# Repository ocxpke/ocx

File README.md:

# OCX handheld: main board

Main PCB of OCX, a PSP-style handheld console designed for my bachelor's thesis (TFG).

## What's on the board
- **MCU:** ESP32-S3-DevKitC-1 on two 1×22 sockets. Its antenna sits over a cutout in the board edge.
- **Display:** BT817Q (EVE4) graphics controller with a W25Q128JV flash and a 12 MHz crystal. It drives a 5" 800×480 RGB panel (NHD-5.0-800480AF-ASXP-CTP) through a 40-pin FPC, and its capacitive touch through a 6-pin FPC.
- **Backlight:** DIO5661 constant-current boost, ~60 mA at ~21 V.
- **Power:** USB-C, 5 V only, with USBLC6-2 ESD protection. An LMR51430 buck makes the 3.3 V rail.
- **Input:** MCP23017 I²C expander for 14 buttons, plus two analog joysticks on FPCs.
- **Audio:** PAM8302A class-D amplifier with a JST PH speaker connector.

## Board
| | |
|---|---|
| EDA | KiCad 10.0 (the files don't open in KiCad 9 or older) |
| Layers | 4: F.Cu signals / In1 GND / In2 3.3 V / B.Cu signals |
| Size | 228 × 115.4 mm, 1.6 mm thick |
| Fab | JLCPCB, JLC04161H-2116 stackup, ENIG |

## Opening the project
Install KiCad 10.0 and open `hardware/ocxPrototype.kicad_pro`.
All footprints and 3D models come from the standard KiCad libraries. The only custom symbol (BT817Q) is in `hardware/EVE_custom.kicad_sym`, registered in the project's `sym-lib-table`.

## License

Copyright © 2026 Jose Ramirez Giron

**Hardware** (everything in `hardware/`: schematics, PCB layout and symbol library) is licensed under the
[CERN Open Hardware Licence Version 2 – Strongly Reciprocal (CERN-OHL-S-2.0)](https://ohwr.org/cern_ohl_s_v2.txt).
See [`LICENSE`](LICENSE) for the full text.

You may use, study, modify, manufacture and sell this design or products based on it, as long as you:
- keep the copyright and licence notices,
- make the source of any modified version available under the same licence, and
- state clearly what you changed and when.

**Documentation and images** (`docs/`) are licensed under
[Creative Commons Attribution-ShareAlike 4.0 (CC BY-SA 4.0)](https://creativecommons.org/licenses/by-sa/4.0/).

"OCX" is the name of this project. Please don't use it for modified versions or present them as the original.

Datasheets of third-party components belong to their manufacturers and are not covered by these licences.

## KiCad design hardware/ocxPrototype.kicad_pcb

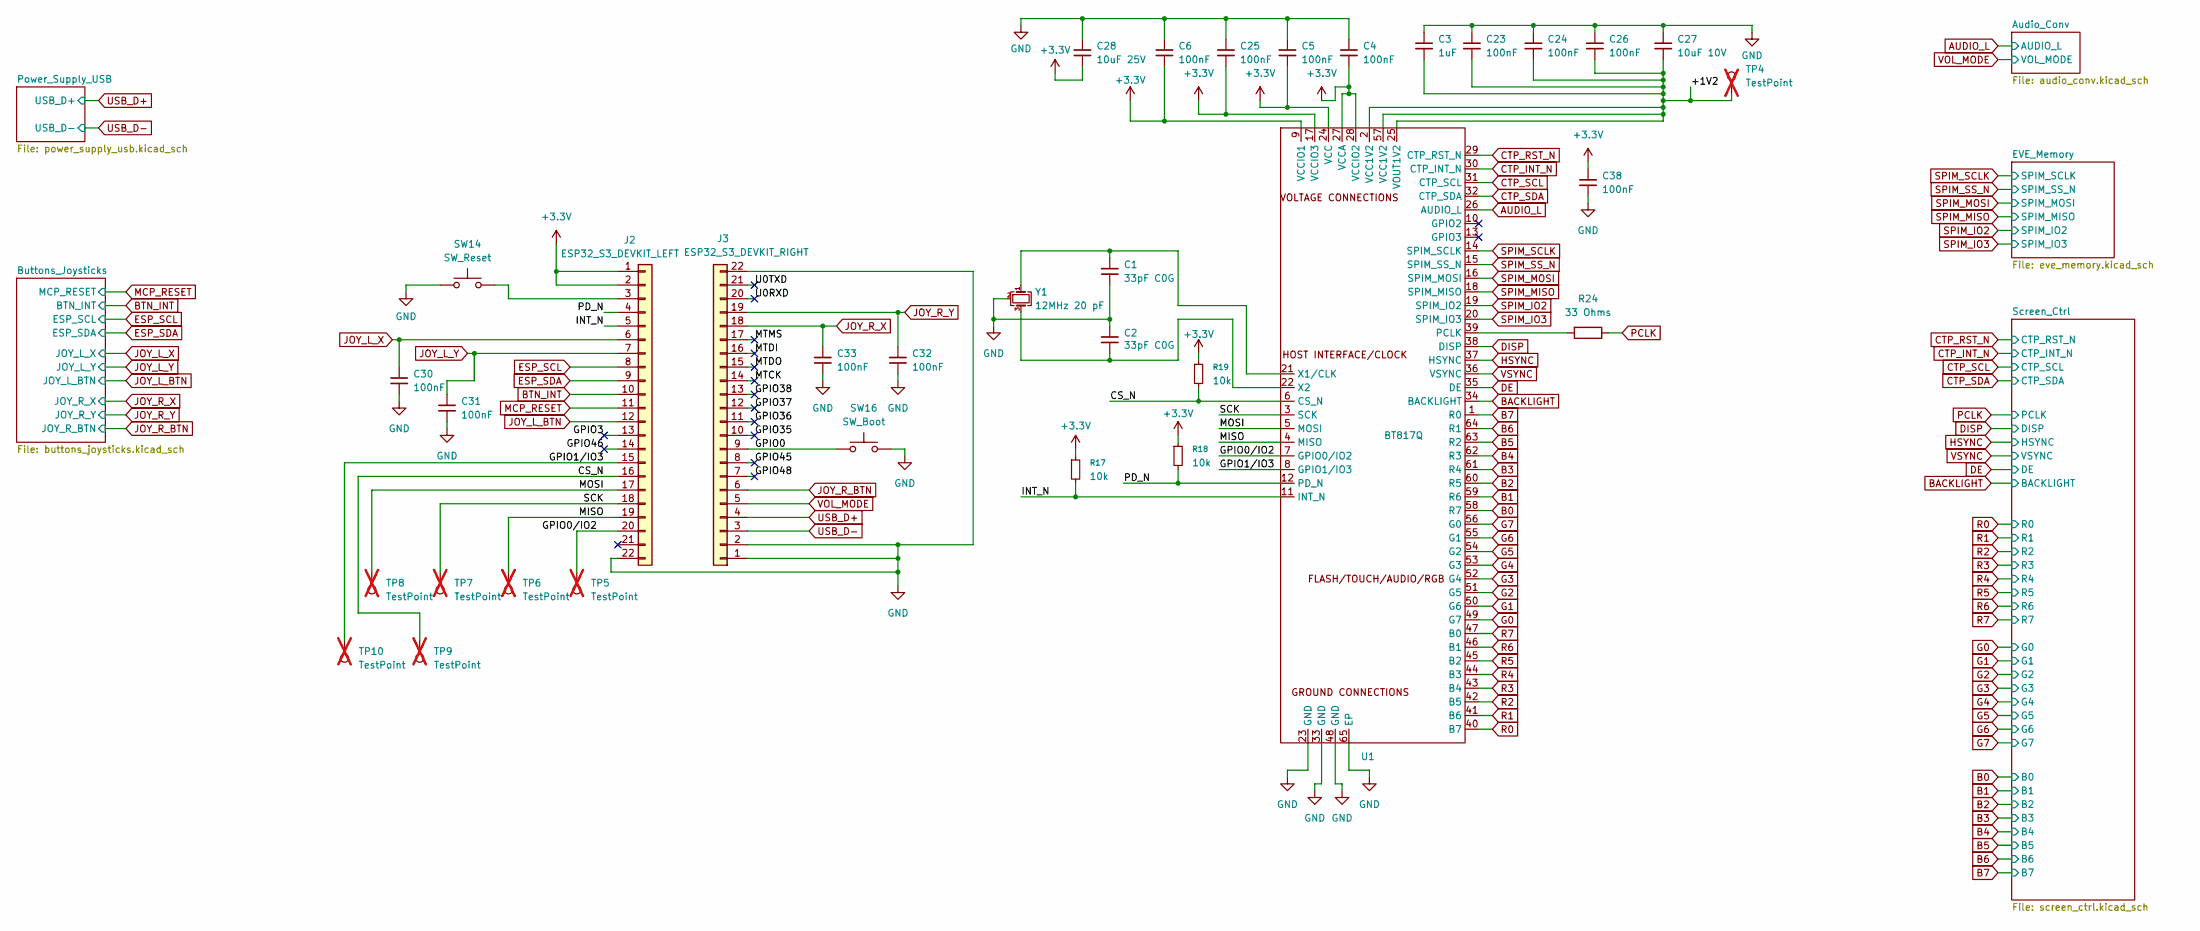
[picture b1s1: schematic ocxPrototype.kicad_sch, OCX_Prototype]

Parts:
C1, C2: 33pF C0G; C_0402_1005Metric; MPN 0402CG330J500NT; LCSC C1562
C3: 1uF; C_0402_1005Metric; MPN CL05A105KA5NQNC; LCSC C52923
C4, C5, C6, C23, C24, C25, C26: 100nF; C_0402_1005Metric; MPN CL05B104KO5NNNC; LCSC C1525
C27: 10uF 10V; C_0603_1608Metric; MPN CL10A106KP8NNNC; LCSC C19702
C28: 10uF 25V; C_0805_2012Metric_Pad1.18x1.45mm_HandSolder; MPN CL21A106KAYNNNE; LCSC C15850
C30, C31, C32, C33, C38: 100nF; C_0805_2012Metric_Pad1.18x1.45mm_HandSolder; MPN CC0805KRX7R9BB104; LCSC C49678
J2: ESP32_S3_DEVKIT_LEFT; PinSocket_1x22_P2.54mm_Vertical; MPN FH2.54-09-22PZD; LCSC C7500786
J3: ESP32_S3_DEVKIT_RIGHT; PinSocket_1x22_P2.54mm_Vertical; MPN FH2.54-09-22PZD; LCSC C7500786
R17, R18, R19: 10k; R_0805_2012Metric_Pad1.20x1.40mm_HandSolder; MPN 0805W8F1002T5E; LCSC C17414
R24: 33 Ohms; R_0402_1005Metric; MPN 0402WGF330JTCE; LCSC C25105
SW14: SW_Reset; SW_PUSH_6mm; MPN MLD-TS-6X6X5-J; LCSC C52750873
SW16: SW_Boot; SW_PUSH_6mm; MPN MLD-TS-6X6X5-J; LCSC C52750873
TP4: TestPoint; TestPoint_Pad_D1.5mm; not fitted
TP5, TP6, TP7, TP8, TP9, TP10: TestPoint; TestPoint_Pad_D1.0mm; not fitted
U1: BT817Q; VQFN-64-1EP_9x9mm_P0.5mm_EP5.4x5.4mm_ThermalVias; MPN BT817Q-R; LCSC C20613585
Y1: 12MHz 20 pF; Crystal_SMD_5032-4Pin_5.0x3.2mm; MPN X503212MSB4SI; LCSC C112588

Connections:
+3.3V: C4.2, C5.2, C6.2, C25.2, C28.2, C38.1, J2.1, J2.2, R17.1, R18.1, R19.1, U1.9 (VCCIO1), U1.17 (VCCIO3), U1.24 (VCC), U1.27 (VCCA), U1.28 (VCCIO2); also elsewhere on the board
/+1V2: C3.2, C23.2, C24.2, C26.2, C27.2, TP4.1 (1_1), U1.2 (VCC1V2), U1.25 (VOUT1V2), U1.57 (VCC1V2)
/CS_N: J2.16, R19.2, TP9.1 (1_1), U1.6 (CS_N)
/GPIO0: J3.9, SW16.1
/GPIO0/IO2: J2.20, TP5.1 (1_1), U1.7 (GPIO0/IO2)
/GPIO1/IO3: J2.15, TP10.1 (1_1), U1.8 (GPIO1/IO3)
/GPIO3: J2.13
/GPIO35: J3.10
/GPIO36: J3.11
/GPIO37: J3.12
/GPIO38: J3.13
/GPIO45: J3.8
/GPIO46: J2.14
/GPIO48: J3.7
/INT_N: J2.5, R17.2, U1.11 (INT_N)
/MISO: J2.19, TP6.1 (1_1), U1.4 (MISO)
/MOSI: J2.17, TP8.1 (1_1), U1.5 (MOSI)
/MTCK: J3.14
/MTDI: J3.16
/MTDO: J3.15
/MTMS: J3.17
/PD_N: J2.4, R18.2, U1.12 (PD_N)
/SCK: J2.18, TP7.1 (1_1), U1.3 (SCK)
/U0RXD: J3.20
/U0TXD: J3.21
AUDIO_L: U1.26 (AUDIO_L); also elsewhere on the board
B0: U1.58 (R7); also elsewhere on the board
B1: U1.59 (R6); also elsewhere on the board
B2: U1.60 (R5); also elsewhere on the board
B3: U1.61 (R4); also elsewhere on the board
B4: U1.62 (R3); also elsewhere on the board
B5: U1.63 (R2); also elsewhere on the board
B6: U1.64 (R1); also elsewhere on the board
B7: U1.1 (R0); also elsewhere on the board
BACKLIGHT: U1.34 (BACKLIGHT); also elsewhere on the board
BTN_INT: J2.10; also elsewhere on the board
CTP_INT_N: U1.30 (CTP_INT_N); also elsewhere on the board
CTP_RST_N: U1.29 (CTP_RST_N); also elsewhere on the board
CTP_SCL: U1.31 (CTP_SCL); also elsewhere on the board
CTP_SDA: U1.32 (CTP_SDA); also elsewhere on the board
DE: U1.35 (DE); also elsewhere on the board
DISP: U1.38 (DISP); also elsewhere on the board
ESP_SCL: J2.8; also elsewhere on the board
ESP_SDA: J2.9; also elsewhere on the board
G0: U1.49 (G7); also elsewhere on the board
G1: U1.50 (G6); also elsewhere on the board
G2: U1.51 (G5); also elsewhere on the board
G3: U1.52 (G4); also elsewhere on the board
G4: U1.53 (G3); also elsewhere on the board
G5: U1.54 (G2); also elsewhere on the board
G6: U1.55 (G1); also elsewhere on the board
G7: U1.56 (G0); also elsewhere on the board
GND: C1.1, C2.2, C3.1, C4.1, C5.1, C6.1, C23.1, C24.1, C25.1, C26.1, C27.1, C28.1, C30.2, C31.2, C32.2, C33.2, C38.2, J2.22, J3.1, J3.2, J3.22, SW14.1, SW16.2, U1.23 (GND), U1.33 (GND), U1.48 (GND), U1.65 (EP), Y1.2 (G), Y1.4 (G); also elsewhere on the board
HSYNC: U1.37 (HSYNC); also elsewhere on the board
JOY_L_BTN: J2.12; also elsewhere on the board
JOY_L_X: C30.1, J2.6; also elsewhere on the board
JOY_L_Y: C31.1, J2.7; also elsewhere on the board
JOY_R_BTN: J3.6; also elsewhere on the board
JOY_R_X: C33.1, J3.18; also elsewhere on the board
JOY_R_Y: C32.1, J3.19; also elsewhere on the board
MCP_RESET: J2.11; also elsewhere on the board
unnamed: J2.3, SW14.2
unnamed: R24.2, U1.39 (PCLK)
unnamed: C1.2, U1.21 (X1/CLK), Y1.1
unnamed: C2.1, U1.22 (X2), Y1.3
PCLK: R24.1; also elsewhere on the board
R0: U1.40 (B7); also elsewhere on the board
R1: U1.41 (B6); also elsewhere on the board
R2: U1.42 (B5); also elsewhere on the board
R3: U1.43 (B4); also elsewhere on the board
R4: U1.44 (B3); also elsewhere on the board
R5: U1.45 (B2); also elsewhere on the board
R6: U1.46 (B1); also elsewhere on the board
R7: U1.47 (B0); also elsewhere on the board
SPIM_IO2: U1.19 (SPIM_IO2); also elsewhere on the board
SPIM_IO3: U1.20 (SPIM_IO3); also elsewhere on the board
SPIM_MISO: U1.18 (SPIM_MISO); also elsewhere on the board
SPIM_MOSI: U1.16 (SPIM_MOSI); also elsewhere on the board
SPIM_SCLK: U1.14 (SPIM_SCLK); also elsewhere on the board
SPIM_SS_N: U1.15 (SPIM_SS_N); also elsewhere on the board
USB_D+: J3.4; also elsewhere on the board
USB_D-: J3.3; also elsewhere on the board
VOL_MODE: J3.5; also elsewhere on the board
VSYNC: U1.36 (VSYNC); also elsewhere on the board

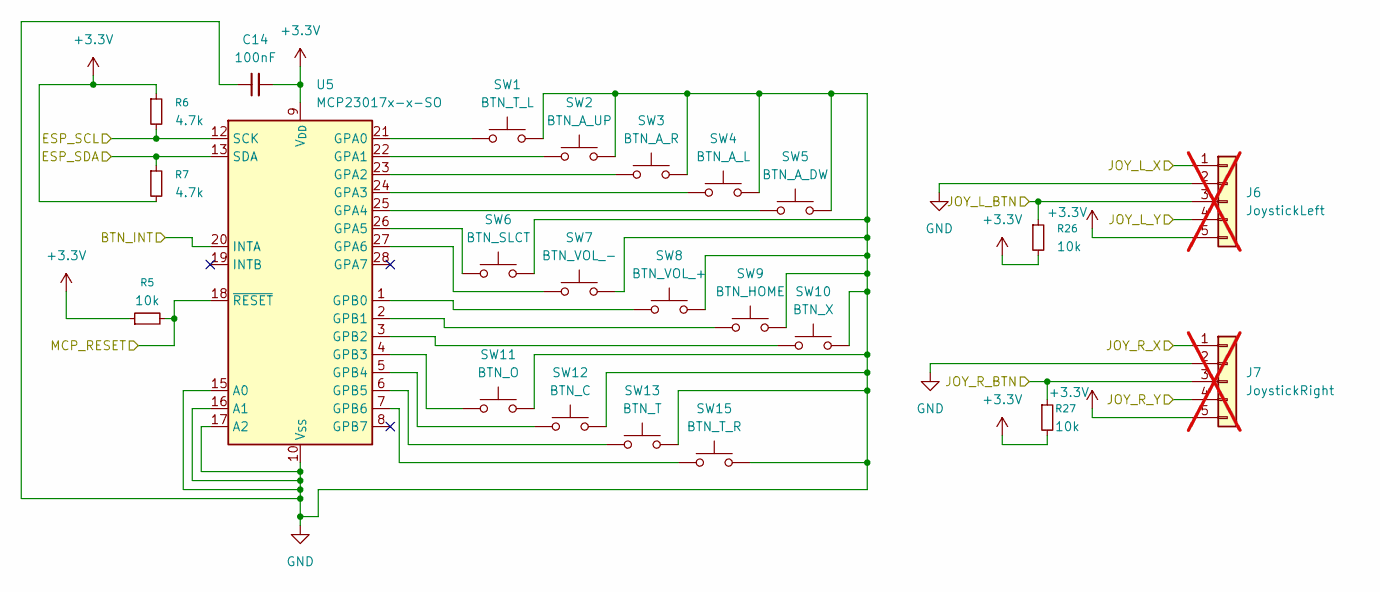
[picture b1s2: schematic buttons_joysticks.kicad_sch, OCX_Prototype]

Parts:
C14: 100nF; C_0805_2012Metric_Pad1.18x1.45mm_HandSolder; MPN CC0805KRX7R9BB104; LCSC C49678
J6: JoystickLeft; TE_0-1734839-5_1x05-1MP_P0.5mm_Horizontal; MPN SFV5R-4STE1HLF; not fitted
J7: JoystickRight; TE_0-1734839-5_1x05-1MP_P0.5mm_Horizontal; MPN SFV5R-4STE1HLF; not fitted
R5, R26, R27: 10k; R_0805_2012Metric_Pad1.20x1.40mm_HandSolder; MPN 0805W8F1002T5E; LCSC C17414
R6, R7: 4.7k; R_0805_2012Metric_Pad1.20x1.40mm_HandSolder; MPN 0805W8F4701T5E; LCSC C17673
SW1: BTN_T_L; SW_PUSH_6mm; MPN MLD-TS-6X6X5-J; LCSC C52750873
SW2: BTN_A_UP; SW_PUSH_6mm; MPN MLD-TS-6X6X5-J; LCSC C52750873
SW3: BTN_A_R; SW_PUSH_6mm; MPN MLD-TS-6X6X5-J; LCSC C52750873
SW4: BTN_A_L; SW_PUSH_6mm; MPN MLD-TS-6X6X5-J; LCSC C52750873
SW5: BTN_A_DW; SW_PUSH_6mm; MPN MLD-TS-6X6X5-J; LCSC C52750873
SW6: BTN_SLCT; SW_PUSH_6mm; MPN MLD-TS-6X6X5-J; LCSC C52750873
SW7: BTN_VOL_-; SW_PUSH_6mm; MPN MLD-TS-6X6X5-J; LCSC C52750873
SW8: BTN_VOL_+; SW_PUSH_6mm; MPN MLD-TS-6X6X5-J; LCSC C52750873
SW9: BTN_HOME; SW_PUSH_6mm; MPN MLD-TS-6X6X5-J; LCSC C52750873
SW10: BTN_X; SW_PUSH_6mm; MPN MLD-TS-6X6X5-J; LCSC C52750873
SW11: BTN_O; SW_PUSH_6mm; MPN MLD-TS-6X6X5-J; LCSC C52750873
SW12: BTN_C; SW_PUSH_6mm; MPN MLD-TS-6X6X5-J; LCSC C52750873
SW13: BTN_T; SW_PUSH_6mm; MPN MLD-TS-6X6X5-J; LCSC C52750873
SW15: BTN_T_R; SW_PUSH_6mm; MPN MLD-TS-6X6X5-J; LCSC C52750873
U5: MCP23017x-x-SO; SOIC-28W_7.5x17.9mm_P1.27mm; MPN MCP23017-E/SO; LCSC C47023

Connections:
+3.3V: C14.2, J6.5, J7.5, R5.1, R6.1, R7.2, R26.2, R27.2, U5.9 (V_{DD}); also elsewhere on the board
BTN_INT: U5.20 (INTA); also elsewhere on the board
ESP_SCL: R6.2, U5.12 (SCK); also elsewhere on the board
ESP_SDA: R7.1, U5.13 (SDA); also elsewhere on the board
GND: C14.1, J6.2, J7.2, SW1.2, SW2.2, SW3.2, SW4.2, SW5.2, SW6.2, SW7.2, SW8.2, SW9.2, SW10.2, SW11.2, SW12.2, SW13.2, SW15.2, U5.10 (V_{SS}), U5.15 (A0), U5.16 (A1), U5.17 (A2); also elsewhere on the board
JOY_L_BTN: J6.3, R26.1; also elsewhere on the board
JOY_L_X: J6.1; also elsewhere on the board
JOY_L_Y: J6.4; also elsewhere on the board
JOY_R_BTN: J7.3, R27.1; also elsewhere on the board
JOY_R_X: J7.1; also elsewhere on the board
JOY_R_Y: J7.4; also elsewhere on the board
MCP_RESET: R5.2, U5.18 (~RESET); also elsewhere on the board
unnamed: SW1.1, U5.21 (GPA0)
unnamed: SW2.1, U5.22 (GPA1)
unnamed: SW3.1, U5.23 (GPA2)
unnamed: SW4.1, U5.24 (GPA3)
unnamed: SW5.1, U5.25 (GPA4)
unnamed: SW6.1, U5.26 (GPA5)
unnamed: SW7.1, U5.27 (GPA6)
unnamed: SW8.1, U5.1 (GPB0)
unnamed: SW9.1, U5.2 (GPB1)
unnamed: SW10.1, U5.3 (GPB2)
unnamed: SW11.1, U5.4 (GPB3)
unnamed: SW12.1, U5.5 (GPB4)
unnamed: SW13.1, U5.6 (GPB5)
unnamed: SW15.1, U5.7 (GPB6)

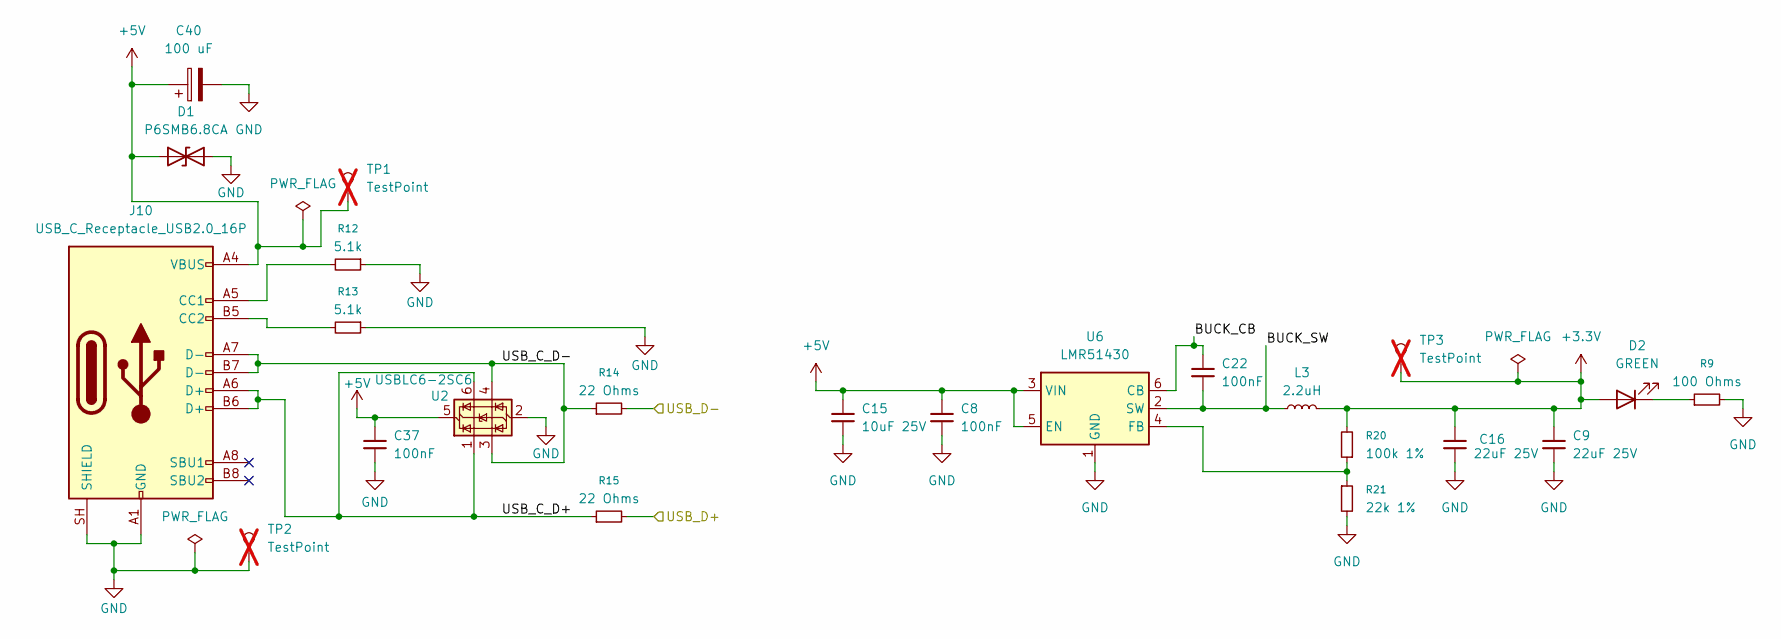
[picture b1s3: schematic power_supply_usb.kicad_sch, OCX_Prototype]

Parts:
C8, C22, C37: 100nF; C_0805_2012Metric_Pad1.18x1.45mm_HandSolder; MPN CC0805KRX7R9BB104; LCSC C49678
C9, C16: 22uF 25V; C_0805_2012Metric_Pad1.18x1.45mm_HandSolder; MPN CL21A226MAQNNNE; LCSC C45783
C15: 10uF 25V; C_0805_2012Metric_Pad1.18x1.45mm_HandSolder; MPN CL21A106KAYNNNE; LCSC C15850
C40: 100 uF; CP_Elec_6.3x5.8; MPN MA16V100M6X6; LCSC C46550460
D1: P6SMB6.8CA; D_SMB_Handsoldering; MPN P6SMB6.8CA/TR13; LCSC C78395
D2: GREEN; LED_0805_2012Metric_Pad1.15x1.40mm_HandSolder; MPN KT-0805G; LCSC C2297
J10: USB_C_Receptacle_USB2.0_16P; USB_C_Receptacle_HRO_TYPE-C-31-M-12; MPN TYPE-C-31-M-12; LCSC C165948
L3: 2.2uH; L_Coilcraft_XxL4020; MPN XAL4020-222MEC; LCSC C3151182
R9: 100 Ohms; R_0805_2012Metric_Pad1.20x1.40mm_HandSolder; MPN 0805W8F1000T5E; LCSC C17408
R12, R13: 5.1k; R_0805_2012Metric_Pad1.20x1.40mm_HandSolder; MPN 0805W8F5101T5E; LCSC C27834
R14, R15: 22 Ohms; R_0805_2012Metric_Pad1.20x1.40mm_HandSolder; MPN 0805W8F220JT5E; LCSC C17561
R20: 100k 1%; R_0805_2012Metric_Pad1.20x1.40mm_HandSolder; MPN 0805W8F1003T5E; LCSC C149504
R21: 22k 1%; R_0805_2012Metric_Pad1.20x1.40mm_HandSolder; MPN 0805W8F2202T5E; LCSC C17560
TP1, TP3: TestPoint; TestPoint_Pad_D1.5mm; not fitted
TP2: TestPoint; TestPoint_Keystone_5000-5004_Miniature; not fitted
U2: USBLC6-2SC6; SOT-23-6; MPN USBLC6-2SC6; LCSC C7519
U6: LMR51430; SOT-23-6; MPN LMR51430YDDCR; LCSC C5210749

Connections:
+3.3V: C9.1, C16.1, D2.2 (A), L3.2, R20.2, TP3.1 (1_1); also elsewhere on the board
/Power_Supply_USB/BUCK_CB: C22.1, U6.6 (CB)
/Power_Supply_USB/BUCK_SW: C22.2, L3.1, U6.2 (SW)
/Power_Supply_USB/USB_C_D+: J10.A6 (D+), J10.B6 (D+), R15.1, U2.1 (I/O1), U2.6 (I/O1)
/Power_Supply_USB/USB_C_D-: J10.A7 (D-), J10.B7 (D-), R14.1, U2.3 (I/O2), U2.4 (I/O2)
GND: C8.2, C9.2, C15.2, C16.2, C37.2, C40.2, D1.2 (A2), J10.A1 (GND), J10.A12 (GND), J10.B1 (GND), J10.B12 (GND), J10.SH (SHIELD), R9.2, R12.1, R13.1, R21.2, TP2.1 (1_1), U2.2 (GND), U6.1 (GND); also elsewhere on the board
unnamed: D2.1 (K), R9.1
unnamed: J10.A5 (CC1), R12.2
unnamed: J10.B5 (CC2), R13.2
unnamed: R20.1, R21.1, U6.4 (FB)
USB_D+: R15.2; also elsewhere on the board
USB_D-: R14.2; also elsewhere on the board

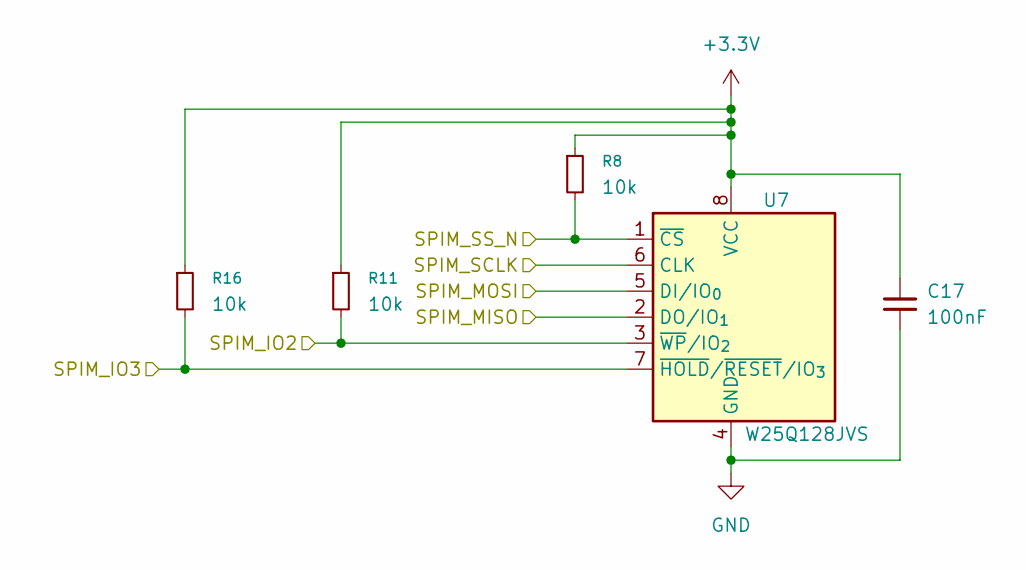
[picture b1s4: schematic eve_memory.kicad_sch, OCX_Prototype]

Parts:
C17: 100nF; C_0402_1005Metric; MPN CL05B104KO5NNNC; LCSC C1525
R8, R11, R16: 10k; R_0805_2012Metric_Pad1.20x1.40mm_HandSolder; MPN 0805W8F1002T5E; LCSC C17414
U7: W25Q128JVS; SOIC-8_5.3x5.3mm_P1.27mm; MPN W25Q128JVSIQ; LCSC C97521

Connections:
+3.3V: C17.1, R8.1, R11.1, R16.1, U7.8 (VCC); also elsewhere on the board
GND: C17.2, U7.4 (GND); also elsewhere on the board
SPIM_IO2: R11.2, U7.3 (~WP/IO_{2}); also elsewhere on the board
SPIM_IO3: R16.2, U7.7 (~HOLD/~RESET/IO_{3}); also elsewhere on the board
SPIM_MISO: U7.2 (DO/IO_{1}); also elsewhere on the board
SPIM_MOSI: U7.5 (DI/IO_{0}); also elsewhere on the board
SPIM_SCLK: U7.6 (CLK); also elsewhere on the board
SPIM_SS_N: R8.2, U7.1 (~CS); also elsewhere on the board

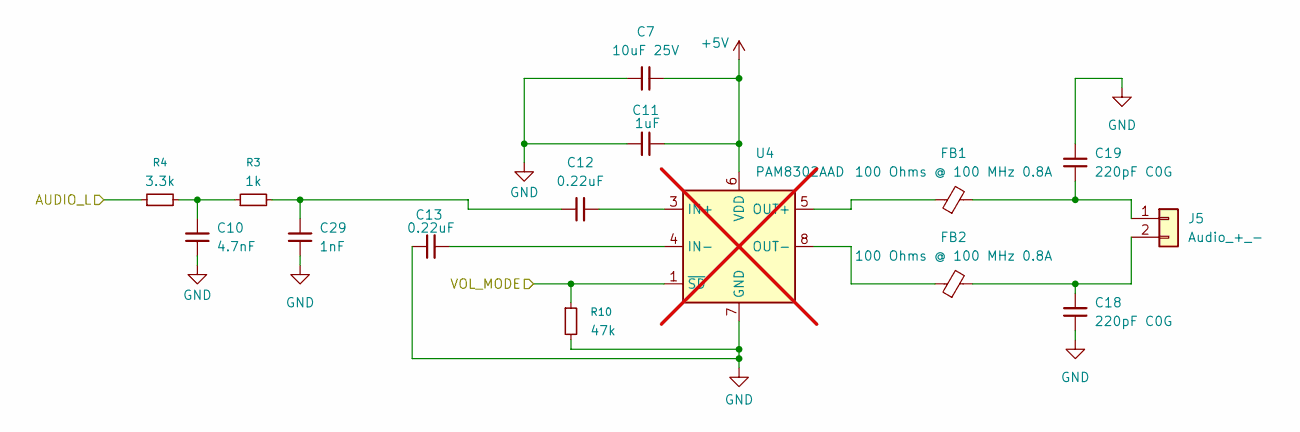
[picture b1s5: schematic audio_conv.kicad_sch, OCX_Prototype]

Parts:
C7: 10uF 25V; C_0805_2012Metric_Pad1.18x1.45mm_HandSolder; MPN CL21A106KAYNNNE; LCSC C15850
C10: 4.7nF; C_0805_2012Metric_Pad1.18x1.45mm_HandSolder; MPN CL21B472KBANNNC; LCSC C50131
C11: 1uF; C_0805_2012Metric_Pad1.18x1.45mm_HandSolder; MPN CL21B105KBFNNNE; LCSC C28323
C12, C13: 0.22uF; C_0805_2012Metric_Pad1.18x1.45mm_HandSolder; MPN CL21B224KBFNNNE; LCSC C5378
C18, C19: 220pF C0G; C_0805_2012Metric_Pad1.18x1.45mm_HandSolder; MPN CC0805JRNPO9BN221; LCSC C107112
C29: 1nF; C_0805_2012Metric_Pad1.18x1.45mm_HandSolder; MPN CL21B102KBCNNNC; LCSC C46653
FB1, FB2: 100 Ohms @ 100 MHz 0.8A; L_0805_2012Metric_Pad1.05x1.20mm_HandSolder; MPN GZ2012D101TF; LCSC C1015
J5: Audio_+_-; JST_PH_B2B-PH-K_1x02_P2.00mm_Vertical; MPN B2B-PH-K-S(LF)(SN); LCSC C131337
R3: 1k; R_0805_2012Metric_Pad1.20x1.40mm_HandSolder; MPN 0805W8F1001T5E; LCSC C17513
R4: 3.3k; R_0805_2012Metric_Pad1.20x1.40mm_HandSolder; MPN 0805W8F3301T5E; LCSC C26010
R10: 47k; R_0805_2012Metric_Pad1.20x1.40mm_HandSolder; MPN 0805W8F4702T5E; LCSC C17713
U4: PAM8302AAD; SOIC-8_3.9x4.9mm_P1.27mm; MPN PAM8302AADCR; not fitted

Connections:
AUDIO_L: R4.1; also elsewhere on the board
GND: C7.1, C10.1, C11.1, C13.1, C18.2, C19.1, C29.2, R10.2, U4.7 (GND); also elsewhere on the board
unnamed: C10.2, R3.1, R4.2
unnamed: C12.1, C29.1, R3.2
unnamed: C19.2, FB1.2, J5.1
unnamed: C18.1, FB2.2, J5.2
unnamed: C12.2, U4.3 (IN+)
unnamed: C13.2, U4.4 (IN-)
unnamed: FB1.1, U4.5 (OUT+)
unnamed: FB2.1, U4.8 (OUT-)
VOL_MODE: R10.1, U4.1 (~SD); also elsewhere on the board

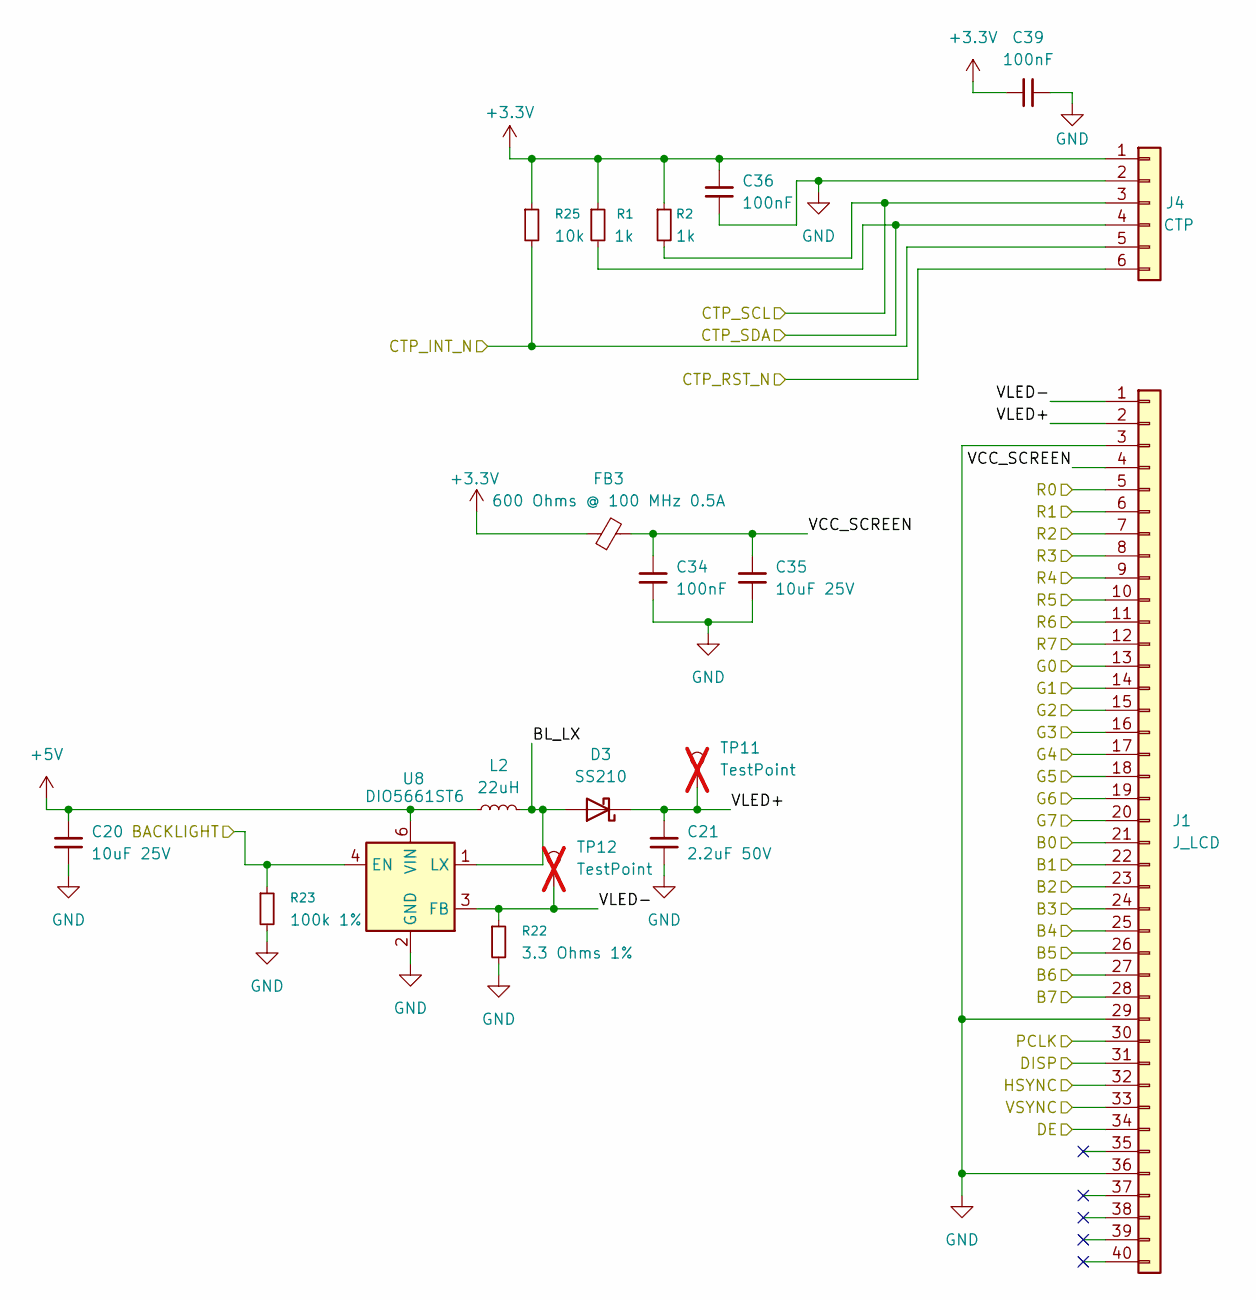
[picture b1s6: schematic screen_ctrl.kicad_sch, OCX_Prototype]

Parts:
C20, C35: 10uF 25V; C_0805_2012Metric_Pad1.18x1.45mm_HandSolder; MPN CL21A106KAYNNNE; LCSC C15850
C21: 2.2uF 50V; C_1206_3216Metric_Pad1.33x1.80mm_HandSolder; MPN CL31B225KBHNNNE; LCSC C50254
C34, C36, C39: 100nF; C_0805_2012Metric_Pad1.18x1.45mm_HandSolder; MPN CC0805KRX7R9BB104; LCSC C49678
D3: SS210; D_SMA_Handsoldering; MPN SS210; LCSC C14996
FB3: 600 Ohms @ 100 MHz 0.5A; L_0805_2012Metric_Pad1.05x1.20mm_HandSolder; MPN GZ2012D601TF; LCSC C1017
J1: J_LCD; Omron_XF2M-4015-1A_1x40-1MP_P0.5mm_Horizontal; MPN XF2M-4015-1A; LCSC C225713
J4: CTP; TE_84953-6_1x06-1MP_P1.0mm_Horizontal; MPN 84953-6; LCSC C408826
L2: 22uH; L_Sunlord_SWPA4030S; MPN FNR4030S220MT; LCSC C167883
R1, R2: 1k; R_0805_2012Metric_Pad1.20x1.40mm_HandSolder; MPN 0805W8F1001T5E; LCSC C17513
R22: 3.3 Ohms 1%; R_0805_2012Metric_Pad1.20x1.40mm_HandSolder; MPN FRC0805F3R30TS; LCSC C2907250
R23: 100k 1%; R_0805_2012Metric_Pad1.20x1.40mm_HandSolder; MPN 0805W8F1003T5E; LCSC C149504
R25: 10k; R_0805_2012Metric_Pad1.20x1.40mm_HandSolder; MPN 0805W8F1002T5E; LCSC C17414
TP11, TP12: TestPoint; TestPoint_Pad_D1.5mm; not fitted
U8: DIO5661ST6; SOT-23-6; MPN DIO5661ST6; LCSC C324576

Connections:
+3.3V: C36.1, C39.1, FB3.1, J4.1, R1.1, R2.1, R25.1; also elsewhere on the board
/Screen_Ctrl/BL_LX: D3.2 (A), L2.2, U8.1 (LX)
/Screen_Ctrl/VCC_SCREEN: C34.1, C35.1, FB3.2, J1.4
/Screen_Ctrl/VLED+: C21.1, D3.1 (K), J1.2, TP11.1 (1_1)
/Screen_Ctrl/VLED-: J1.1, R22.1, TP12.1 (1_1), U8.3 (FB)
B0: J1.21; also elsewhere on the board
B1: J1.22; also elsewhere on the board
B2: J1.23; also elsewhere on the board
B3: J1.24; also elsewhere on the board
B4: J1.25; also elsewhere on the board
B5: J1.26; also elsewhere on the board
B6: J1.27; also elsewhere on the board
B7: J1.28; also elsewhere on the board
BACKLIGHT: R23.1, U8.4 (EN); also elsewhere on the board
CTP_INT_N: J4.5, R25.2; also elsewhere on the board
CTP_RST_N: J4.6; also elsewhere on the board
CTP_SCL: J4.3, R2.2; also elsewhere on the board
CTP_SDA: J4.4, R1.2; also elsewhere on the board
DE: J1.34; also elsewhere on the board
DISP: J1.31; also elsewhere on the board
G0: J1.13; also elsewhere on the board
G1: J1.14; also elsewhere on the board
G2: J1.15; also elsewhere on the board
G3: J1.16; also elsewhere on the board
G4: J1.17; also elsewhere on the board
G5: J1.18; also elsewhere on the board
G6: J1.19; also elsewhere on the board
G7: J1.20; also elsewhere on the board
GND: C20.2, C21.2, C34.2, C35.2, C36.2, C39.2, J1.3, J1.29, J1.36, J4.2, R22.2, R23.2, U8.2 (GND); also elsewhere on the board
HSYNC: J1.32; also elsewhere on the board
PCLK: J1.30; also elsewhere on the board
R0: J1.5; also elsewhere on the board
R1: J1.6; also elsewhere on the board
R2: J1.7; also elsewhere on the board
R3: J1.8; also elsewhere on the board
R4: J1.9; also elsewhere on the board
R5: J1.10; also elsewhere on the board
R6: J1.11; also elsewhere on the board
R7: J1.12; also elsewhere on the board
VSYNC: J1.33; also elsewhere on the board

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
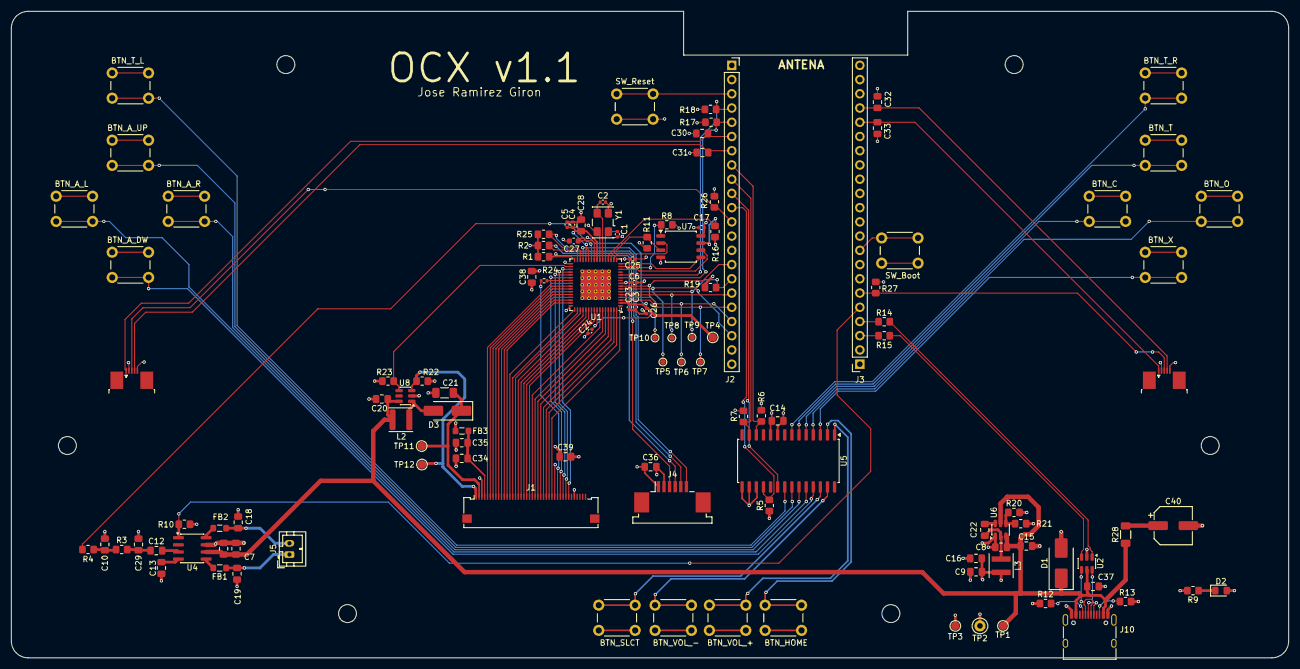
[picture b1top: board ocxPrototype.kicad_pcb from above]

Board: 4 copper layers, 228.0 x 115.4 mm, 120 parts (0 on the bottom side), 106 nets.

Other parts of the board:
R28: 0.1 Ohms 1%; R_1206_3216Metric_Pad1.30x1.75mm_HandSolder

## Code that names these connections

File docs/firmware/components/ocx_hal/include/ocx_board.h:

/*
 * ocx_board.h — Asignación de pines de la placa OCX (Fab v1.0).
 *
 * Verificado contra hardware/ocxPrototype.kicad_sch y
 * hardware/buttons_joysticks.kicad_sch (conectores J2/J3 del DevKitC-1).
 */
#ifndef OCX_BOARD_H
#define OCX_BOARD_H

/* ---- BT817Q (EVE4) por QSPI ------------------------------------------- *
 * Son exactamente los pines IO_MUX de SPI2 (FSPI) en la ESP32-S3, así que
 * el bus no pasa por la matriz GPIO.                                      */
#define OCX_PIN_EVE_SCLK   12 /* FSPICLK  → BT817 SCK            */
#define OCX_PIN_EVE_IO0    11 /* FSPID    → BT817 MOSI/IO0       */
#define OCX_PIN_EVE_IO1    13 /* FSPIQ    → BT817 MISO/IO1       */
#define OCX_PIN_EVE_IO2    14 /* FSPIWP   → BT817 GPIO0/IO2      */
#define OCX_PIN_EVE_IO3     9 /* FSPIHD   → BT817 GPIO1/IO3      */
#define OCX_PIN_EVE_CS     10 /* FSPICS0  → BT817 CS_N           */
#define OCX_PIN_EVE_PD_N    4 /* salida   → BT817 PD_N           */
#define OCX_PIN_EVE_INT_N   5 /* entrada  ← BT817 INT_N          */

/* ---- MCP23017 (14 botones) -------------------------------------------- */
#define OCX_PIN_I2C_SCL    15
#define OCX_PIN_I2C_SDA    16
#define OCX_PIN_MCP_INT    17 /* INTA; INTB sin conectar → IOCON.MIRROR = 1 */
#define OCX_PIN_MCP_RESET  18 /* activo a nivel bajo, pull-up 10 k (R5)      */
#define OCX_MCP_I2C_ADDR   0x20 /* A2..A0 a GND */
#define OCX_I2C_HZ         400000

/* ---- Joysticks (ADC1) y sus pulsadores -------------------------------- */
#define OCX_PIN_JOY_L_X     6 /* ADC1_CH5 */
#define OCX_PIN_JOY_L_Y     7 /* ADC1_CH6 */
#define OCX_PIN_JOY_R_X     2 /* ADC1_CH1 */
#define OCX_PIN_JOY_R_Y     1 /* ADC1_CH0 */
#define OCX_PIN_JOY_L_BTN   8 /* a GND al pulsar, pull-up interno */
#define OCX_PIN_JOY_R_BTN  47 /* a GND al pulsar, pull-up interno */

/* ---- Audio ------------------------------------------------------------- *
 * La señal sale del BT817 (AUDIO_L, PWM) al PAM8302A. GPIO21 = ~SD:
 * 1 = amplificador activo, 0 = apagado.                                    */
#define OCX_PIN_AMP_SD     21

#endif /* OCX_BOARD_H */
